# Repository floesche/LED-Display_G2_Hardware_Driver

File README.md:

---
title: LED Array PCBs
parent: Generation 2
---

## Project content

```
├── led_array_3mm
│   └── gerber_v0p1
├── led_array_3mm_spacer
├── led_array_5mm
│   └── gerber_v0p1
├── led_array_5mm_adaptor
│   └── gerber_v0p1
├── led_array_5mm_mask
│   ├── arrayed
│   └── single
├── led_array_8x8_template
├── led_array_mixed
│   ├── gerber_v0p1
│   └── gerber_v0p2
├── led_array_sm0805
│   └── gerber_v0p1
└── pass_thru_panel
    └── gerber_v1p0
```

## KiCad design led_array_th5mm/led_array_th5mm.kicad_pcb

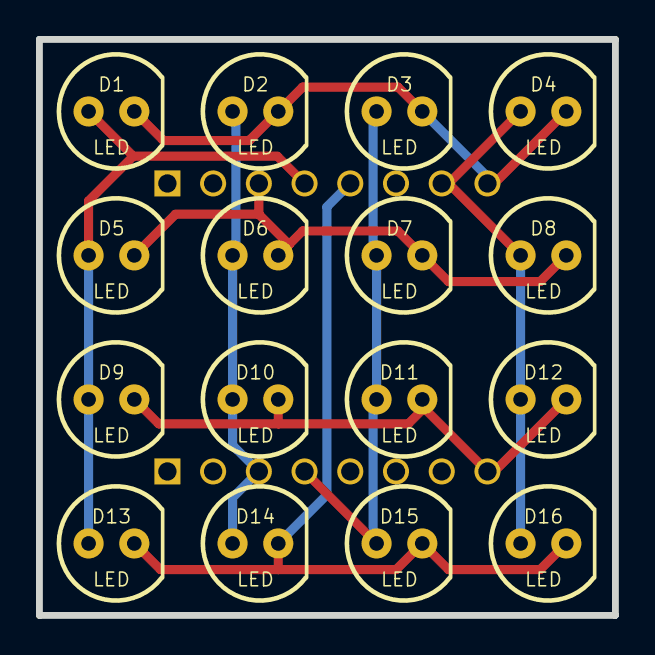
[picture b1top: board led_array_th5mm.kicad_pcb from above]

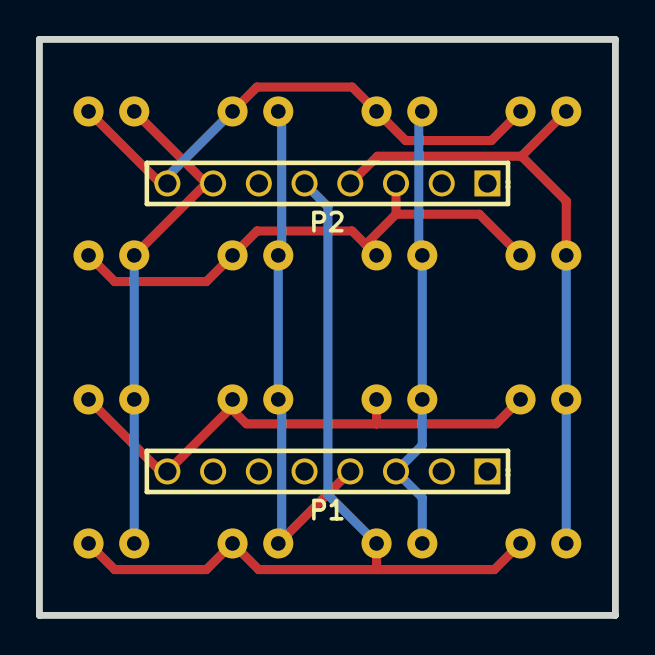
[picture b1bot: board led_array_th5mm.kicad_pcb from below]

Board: 2 copper layers, 32.0 x 32.0 mm, 18 parts (2 on the bottom side), 8 nets.

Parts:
D1, D2, D3, D4, D5, D6, D7, D8, D9, D10, D11, D12, D13, D14, D15, D16: LED; LED-5MM-MOD
P1, P2: PIN_ARRAY-8X1

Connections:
/3: D2.1, D6.1, D10.1, D14.1, P1.3
/4: D3.1, D7.1, D11.1, D15.1, P1.4
/8: D9.2, D10.2, D11.2, D12.2, P1.8
/9: D1.2, D2.2, D3.2, D4.2, P2.8
/10: D4.1, D8.1, D12.1, D16.1, P2.7
/12: D13.2, D14.2, D15.2, D16.2, P2.5
/13: D1.1, D5.1, D9.1, D13.1, P2.4
/14: D5.2, D6.2, D7.2, D8.2, P2.3

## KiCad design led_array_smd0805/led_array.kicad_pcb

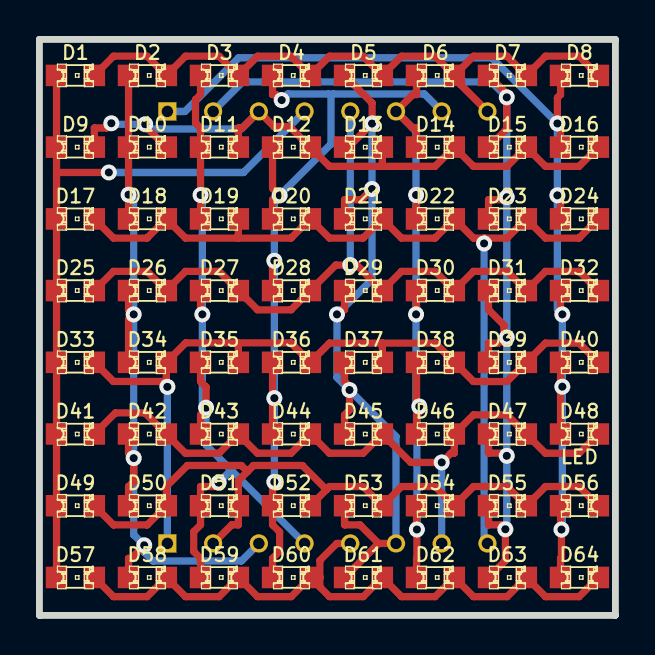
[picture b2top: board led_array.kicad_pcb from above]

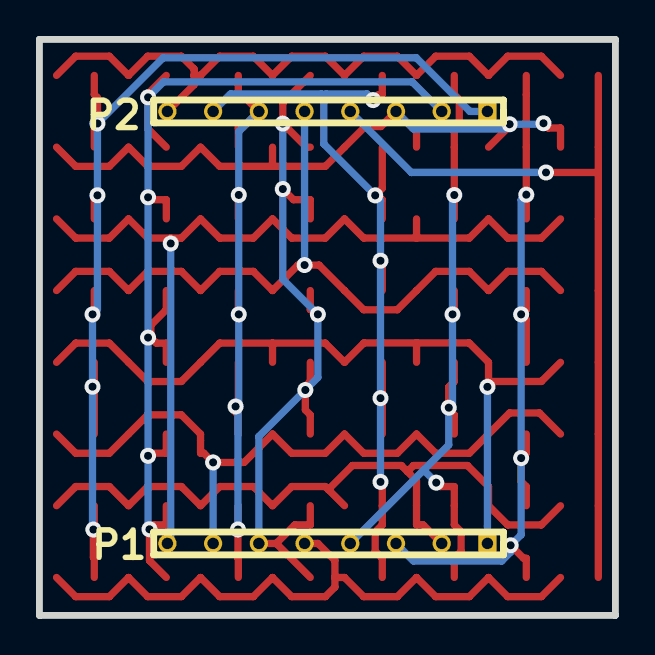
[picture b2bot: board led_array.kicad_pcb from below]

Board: 2 copper layers, 32.0 x 32.0 mm, 66 parts (2 on the bottom side), 16 nets.

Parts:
D1, D2, D3, D4, D5, D6, D7, D8, D9, D10, D11, D12, D13, D14, D15, D16, D17, D18, D19, D20, D21, D22, D23, D24, D25, D26, D27, D28, D29, D30, D31, D32, D33, D34, D35, D36, D37, D38, D39, D40, D41, D42, D43, D44, D45, D46, D47, D49, D50, D51, D52, D53, D54, D55, D56, D57, D58, D59, D60, D61, D62, D63, D64: LED-0805
D48: LED; LED-0805
P1, P2: PANEL_HEADER_8PIN

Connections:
/1: D33.2, D34.2, D35.2, D36.2, D37.2, D38.2, D39.2, D40.2, P1.1
/2: D49.2, D50.2, D51.2, D52.2, D53.2, D54.2, D55.2, D56.2, P1.2
/3: D2.1, D10.1, D18.1, D26.1, D34.1, D42.1, D50.1, D58.1, P1.3
/4: D3.1, D11.1, D19.1, D27.1, D35.1, D43.1, D51.1, D59.1, P1.4
/5: D57.2, D58.2, D59.2, D60.2, D61.2, D62.2, D63.2, D64.2, P1.5
/6: D5.1, D13.1, D21.1, D29.1, D37.1, D45.1, D53.1, D61.1, P1.6
/7: D41.2, D42.2, D43.2, D44.2, D45.2, D46.2, D47.2, D48.2, P1.7
/8: D17.2, D18.2, D19.2, D20.2, D21.2, D22.2, D23.2, D24.2, P1.8
/9: D1.2, D2.2, D3.2, D4.2, D5.2, D6.2, D7.2, D8.2, P2.8
/10: D4.1, D12.1, D20.1, D28.1, D36.1, D44.1, D52.1, D60.1, P2.7
/11: D6.1, D14.1, D22.1, D30.1, D38.1, D46.1, D54.1, D62.1, P2.6
/12: D25.2, D26.2, D27.2, D28.2, D29.2, D30.2, D31.2, D32.2, P2.5
/13: D1.1, D9.1, D17.1, D25.1, D33.1, D41.1, D49.1, D57.1, P2.4
/14: D9.2, D10.2, D11.2, D12.2, D13.2, D14.2, D15.2, D16.2, P2.3
/15: D7.1, D15.1, D23.1, D31.1, D39.1, D47.1, D55.1, D63.1, P2.2
/16: D8.1, D16.1, D24.1, D32.1, D40.1, D48.1, D56.1, D64.1, P2.1

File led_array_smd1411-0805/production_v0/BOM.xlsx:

Item # | Qty | Reference | Descritpion | P/N | Vendor
1 | 32 | D1, D3, D5, D7, D10, D12, D14, D16, D17, D19, D21, D23, D26, D28, D30, D32, D33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 | LED 570nm (green) SMD 0805 | 511-1287-1-ND | Digikey
2 | 32 | D2, D4, D6, D8, D9, D11, D13, D15, D18, D20, D22, D24, D25, D27, D29, D31, D34,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 | LED 365nm (UV) SMD | YLUV-365SMD | Shanghai Yuli Technology Co., Ltd (For contact information see below)
3 | 2 | P1, P2 | SMD header – 8 pos made from 64 pos breakaway | ED24064-ND | Digikey
Notes:
1.) Components P1 and P2 on the back side of the PCB are not to be included in 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
2.) Shanghai Yuli Technology Co., Ltd. Contact: Luna Tang, Email: sales@yulitec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

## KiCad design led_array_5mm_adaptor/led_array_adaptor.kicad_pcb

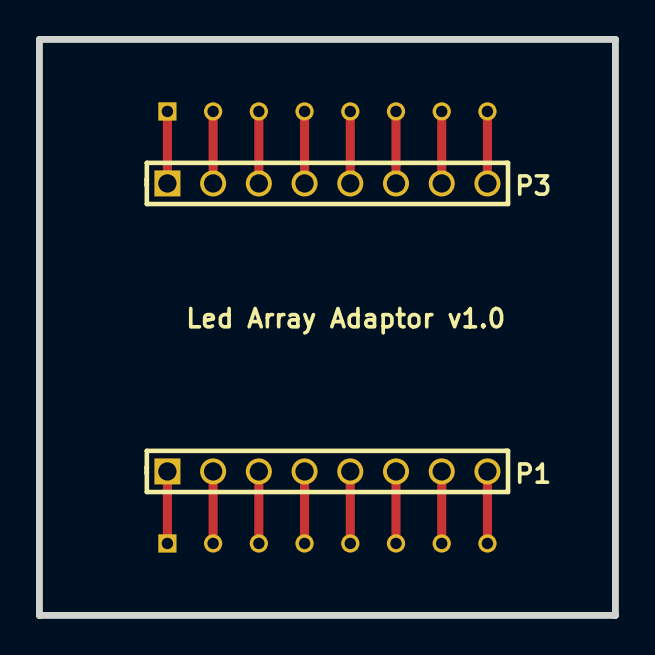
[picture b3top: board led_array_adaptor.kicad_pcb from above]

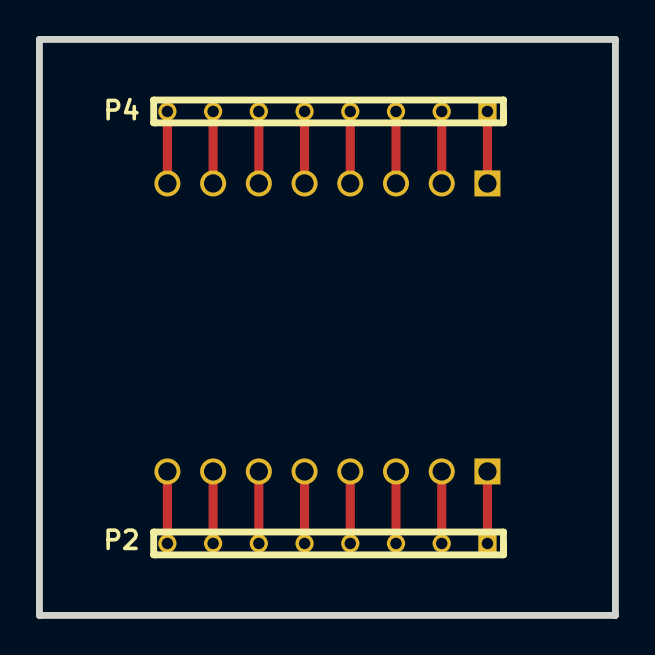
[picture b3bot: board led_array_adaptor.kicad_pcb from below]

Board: 2 copper layers, 32.0 x 32.0 mm, 4 parts (2 on the bottom side), 16 nets.

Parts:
P1, P3: PIN_ARRAY-8X1
P2, P4: PANEL_HEADER_8PIN

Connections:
unnamed: P3.1, P4.1
unnamed: P3.2, P4.2
unnamed: P3.3, P4.3
unnamed: P3.4, P4.4
unnamed: P3.5, P4.5
unnamed: P3.6, P4.6
unnamed: P3.7, P4.7
unnamed: P3.8, P4.8
unnamed: P1.1, P2.1
unnamed: P1.2, P2.2
unnamed: P1.3, P2.3
unnamed: P1.4, P2.4
unnamed: P1.5, P2.5
unnamed: P1.6, P2.6
unnamed: P1.7, P2.7
unnamed: P1.8, P2.8

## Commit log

2020-08-06 getting ready for panel page
2021-11-11 cleanup 3mm
2021-11-11 add footprint library
2021-11-11 5mm cleanup
2021-11-11 cleanup adaptor
2021-11-11 clean up template
2021-11-11 cleanup mixed
2021-11-11 cleanup sm0805
2021-11-11 cleanup pass thru
2021-11-11 project renames
2021-11-11 add 0805 documentation
2021-11-11 start 1411 0805 documentation
2021-11-11 move production files
2021-11-11 rename production files
2021-11-11 rename template
2021-11-11 add template documentation
2021-11-11 project rename
2021-11-11 docs for 5mm
2021-11-11 rename panel adaptor
2021-11-11 improve pass through documentation
2021-11-11 make license more readable; add readme
2021-11-12 change menu order
2021-11-19 improve file size
2021-11-30 consistent documentation
2022-11-08 fix link
2022-11-08 fix links
